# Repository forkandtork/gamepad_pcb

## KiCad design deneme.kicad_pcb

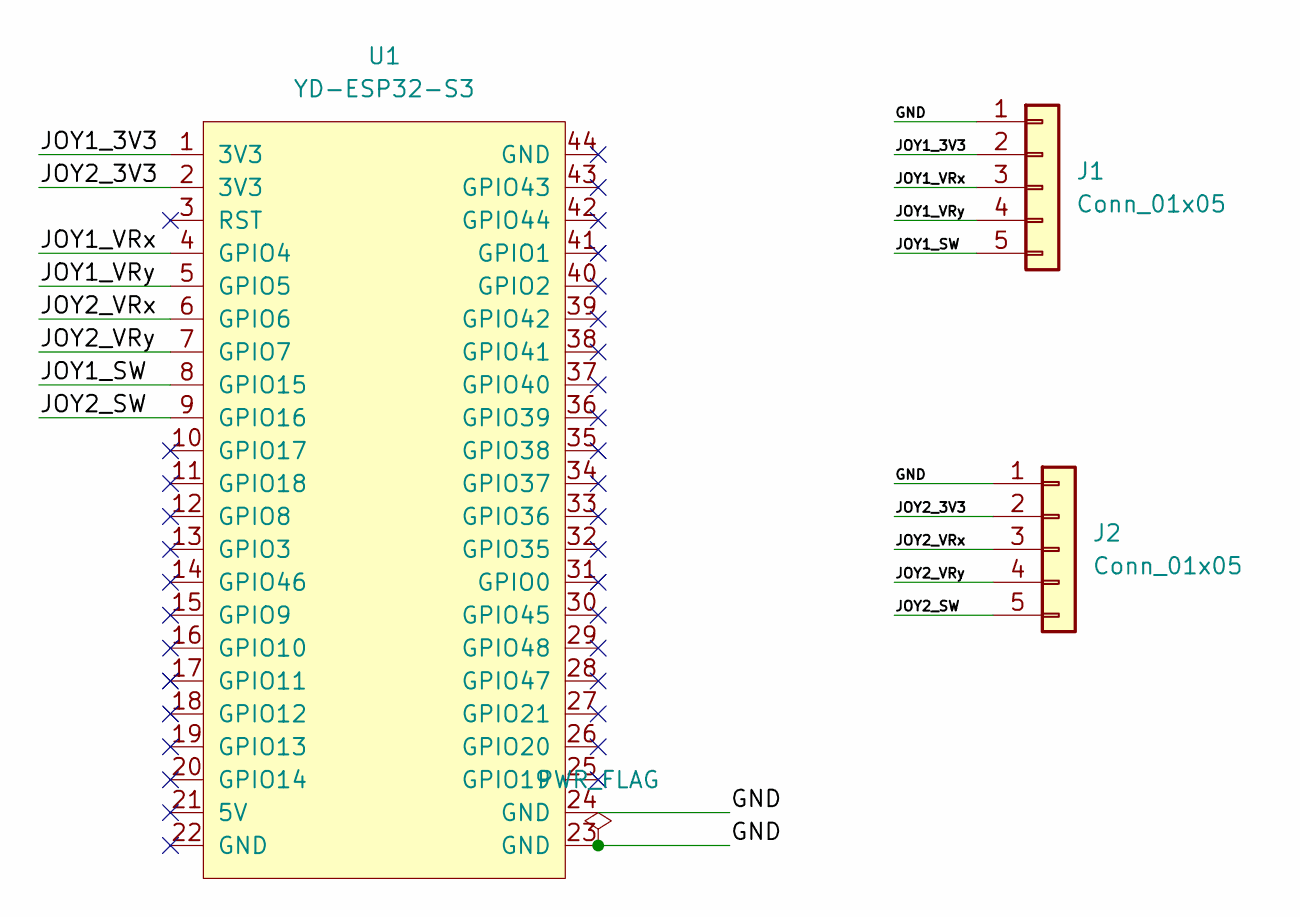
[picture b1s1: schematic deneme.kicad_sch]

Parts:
J1, J2: Conn_01x05; PinHeader_1x05_P2.54mm_Vertical
U1: YD-ESP32-S3

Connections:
/GND: J1.1, J2.1, U1.23 (GND), U1.24 (GND)
/JOY1_3V3: J1.2, U1.1 (3V3)
/JOY1_SW: J1.5, U1.8 (GPIO15)
/JOY1_VRx: J1.3, U1.4 (GPIO4)
/JOY1_VRy: J1.4, U1.5 (GPIO5)
/JOY2_3V3: J2.2, U1.2 (3V3)
/JOY2_SW: J2.5, U1.9 (GPIO16)
/JOY2_VRx: J2.3, U1.6 (GPIO6)
/JOY2_VRy: J2.4, U1.7 (GPIO7)

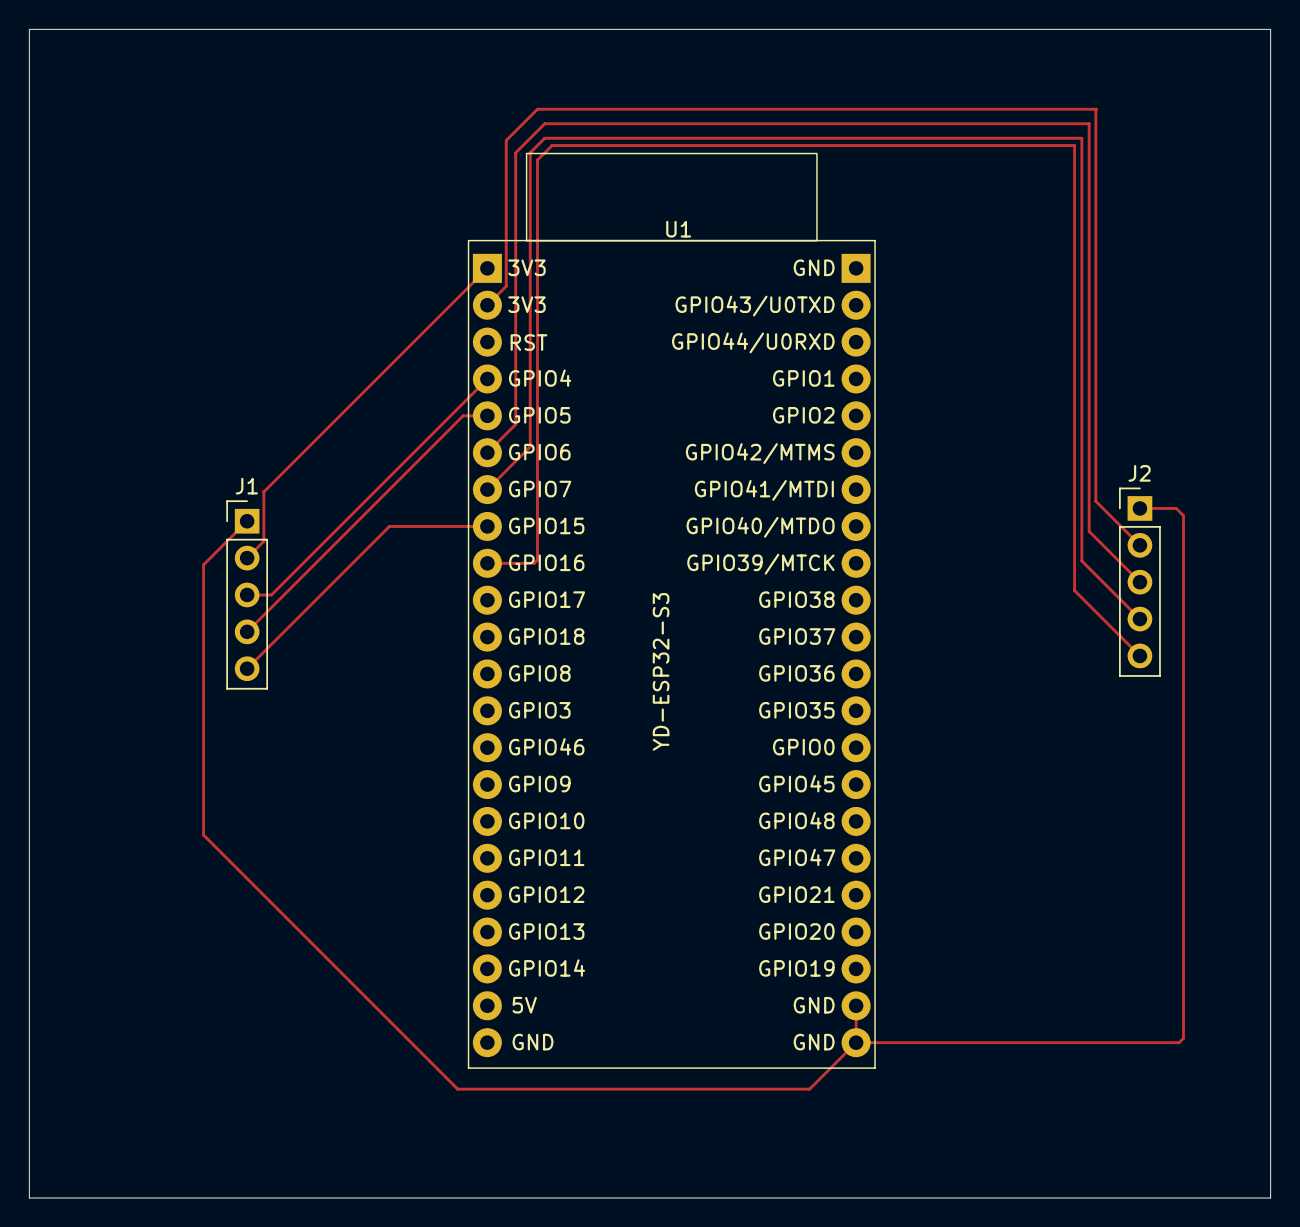
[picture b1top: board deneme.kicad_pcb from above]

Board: 2 copper layers, 85.5 x 80.5 mm, 3 parts (0 on the bottom side), 9 nets.
